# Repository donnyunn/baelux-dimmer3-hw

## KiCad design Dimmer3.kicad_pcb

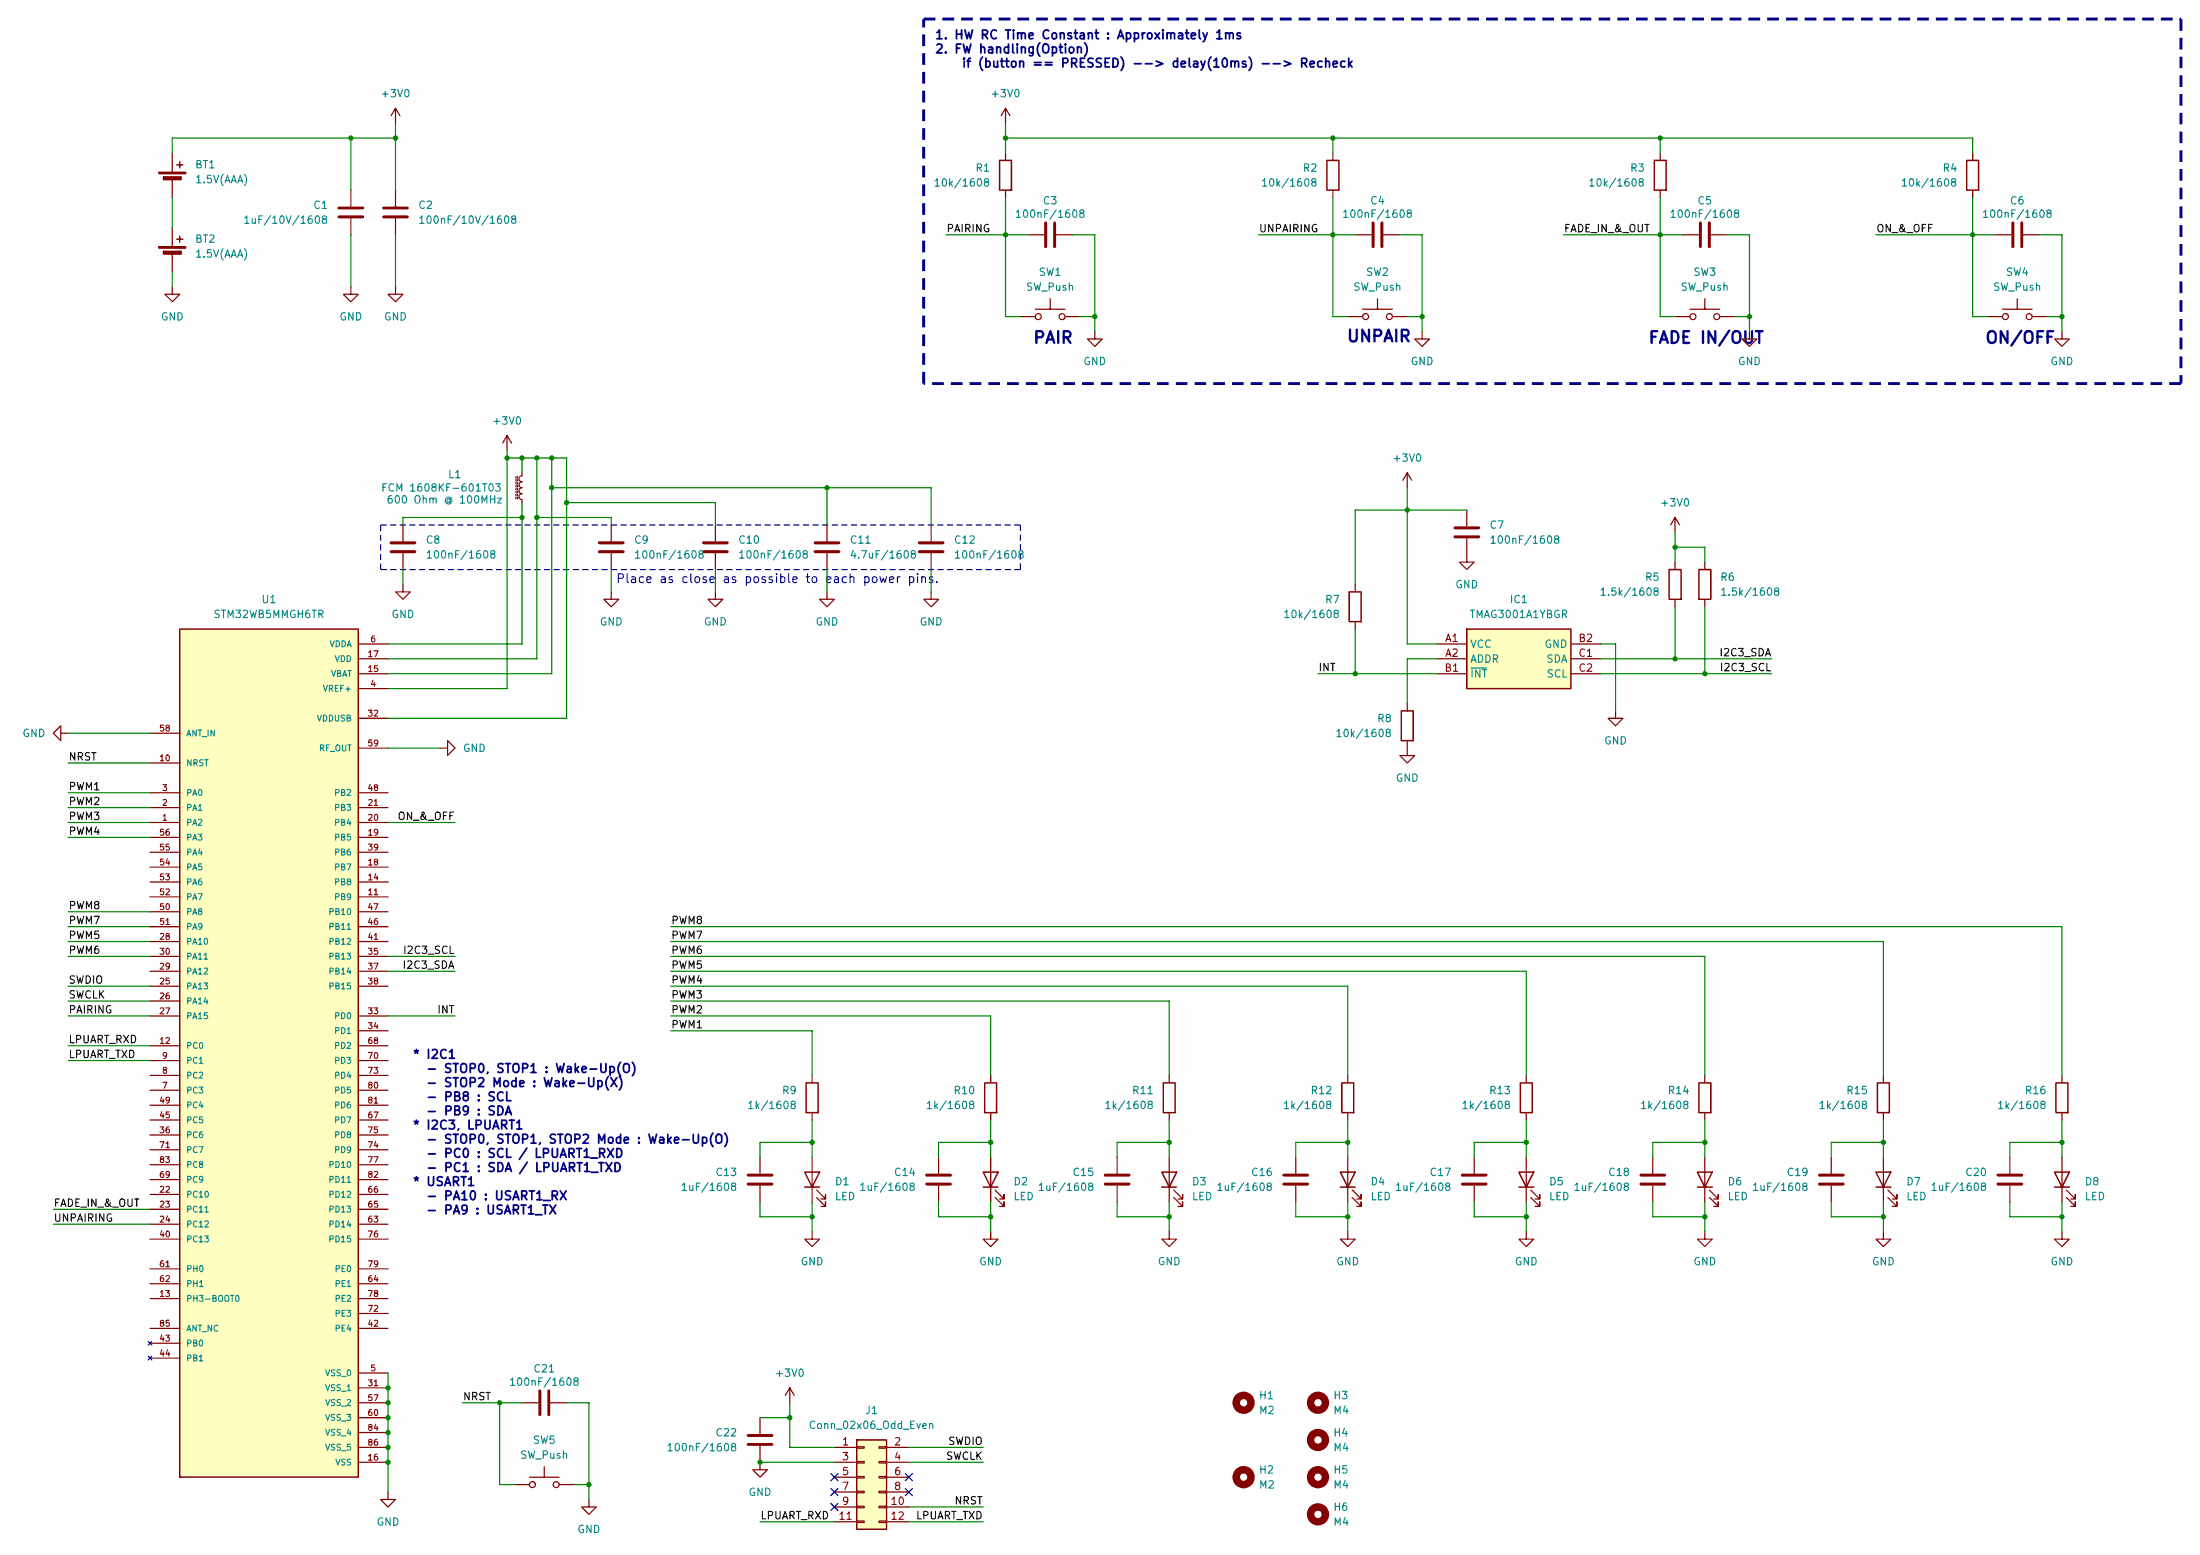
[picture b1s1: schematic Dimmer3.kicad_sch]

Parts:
BT1, BT2: 1.5V(AAA); Battery_spring
C1: 1uF/10V/1608; C_0603_1608Metric; MPN 0603F105Z100CT; LCSC Part# C302042
C2: 100nF/10V/1608; C_0603_1608Metric; MPN CGA0603X7R104K100JT; LCSC Part# C36911391
C3, C4, C5, C6, C7, C8, C9, C10, C12, C21, C22: 100nF/1608; C_0603_1608Metric; MPN CGA0603X7R104K100JT; LCSC Part# C36911391
C11: 4.7uF/1608; C_0603_1608Metric; MPN CL10A475KO8NNNC; LCSC Part# C19666
C13, C14, C15, C16, C17, C18, C19, C20: 1uF/1608; C_0603_1608Metric; MPN 0603F105Z100CT; LCSC Part# C302042
D1, D2, D3, D4, D5, D6, D7, D8: LED; LED_MP-3014-1100-50-80; MPN HL-A-3014S31YC-S1-08HL; LCSC Part# C784732
H1, H2: M2; MountingHole_2.2mm_M2
H3, H4, H5, H6: M4; MountingHole_4.3mm_M4
IC1: TMAG3001A1YBGR; BGA6C40P2X3_79X129X50; Mouser Part Number 595-TMAG3001A1YBGR
J1: Conn_02x06_Odd_Even; PinHeader_2x06_P1.27mm_Vertical
L1: FCM 1608KF-601T03; L_0603_1608Metric_Pad1.05x0.95mm_HandSolder; MPN FCM1608KF-601T03; LCSC Part# C141723
R1, R2, R3, R4, R7, R8: 10k/1608; R_0603_1608Metric; MPN RC0603FR-0710KL; LCSC Part# C98220
R5, R6: 1.5k/1608; R_0603_1608Metric; MPN RC0603FR-071K5L; LCSC Part# C114668
R9, R10, R11, R12, R13, R14, R15, R16: 1k/1608; R_0603_1608Metric; MPN RC0603FR-071KL; LCSC Part# C22548
SW1, SW2, SW3, SW4, SW5: SW_Push; SW_Push_1P1T_XKB_TS-1187A; MPN TS-1087S-01526; LCSC Part# C455262
U1: STM32WB5MMGH6TR; XCVR_STM32WB5MMGH6TR; PARTREV Rev 2; LCSC Part# C5184586

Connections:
+3V0: BT1.1 (+), C1.1, C2.1, C7.1, C9.1, C10.1, C11.1, C12.1, C22.1, IC1.A1 (VCC), J1.1, L1.1, R1.1, R2.1, R3.1, R4.1, R5.1, R6.1, R7.1, U1.4 (VREF+), U1.15 (VBAT), U1.17 (VDD), U1.32 (VDDUSB)
/FADE_IN_&_OUT: C5.1, R3.2, SW3.1, U1.23 (PC11)
/I2C3_SCL: IC1.C2 (SCL), R6.2, U1.35 (PB13)
/I2C3_SDA: IC1.C1 (SDA), R5.2, U1.37 (PB14)
/INT: IC1.B1 (~INT), R7.2, U1.33 (PD0)
/LPUART_RXD: J1.11, U1.12 (PC0)
/LPUART_TXD: J1.12, U1.9 (PC1)
/NRST: C21.1, J1.10, SW5.1, U1.10 (NRST)
/ON_&_OFF: C6.1, R4.2, SW4.1, U1.20 (PB4)
/PAIRING: C3.1, R1.2, SW1.1, U1.27 (PA15)
/PWM1: R9.1, U1.3 (PA0)
/PWM2: R10.1, U1.2 (PA1)
/PWM3: R11.1, U1.1 (PA2)
/PWM4: R12.1, U1.56 (PA3)
/PWM5: R13.1, U1.28 (PA10)
/PWM6: R14.1, U1.30 (PA11)
/PWM7: R15.1, U1.51 (PA9)
/PWM8: R16.1, U1.50 (PA8)
/SWCLK: J1.4, U1.26 (PA14)
/SWDIO: J1.2, U1.25 (PA13)
/UNPAIRING: C4.1, R2.2, SW2.1, U1.24 (PC12)
GND: BT2.2 (-), C1.2, C2.2, C3.2, C4.2, C5.2, C6.2, C7.2, C8.2, C9.2, C10.2, C11.2, C12.2, C13.2, C14.2, C15.2, C16.2, C17.2, C18.2, C19.2, C20.2, C21.2, C22.2, D1.1 (K), D2.1 (K), D3.1 (K), D4.1 (K), D5.1 (K), D6.1 (K), D7.1 (K), D8.1 (K), IC1.B2 (GND), J1.3, R8.2, SW1.2, SW2.2, SW3.2, SW4.2, SW5.2, U1.5 (VSS_0), U1.16 (VSS), U1.31 (VSS_1), U1.57 (VSS_2), U1.58 (ANT_IN), U1.59 (RF_OUT), U1.60 (VSS_3), U1.84 (VSS_4), U1.86 (VSS_5)
unnamed: C13.1, D1.2 (A), R9.2
unnamed: C14.1, D2.2 (A), R10.2
unnamed: C15.1, D3.2 (A), R11.2
unnamed: C16.1, D4.2 (A), R12.2
unnamed: C17.1, D5.2 (A), R13.2
unnamed: C18.1, D6.2 (A), R14.2
unnamed: C19.1, D7.2 (A), R15.2
unnamed: C20.1, D8.2 (A), R16.2
unnamed: IC1.A2 (ADDR), R8.1
unnamed: C8.1, L1.2, U1.6 (VDDA)

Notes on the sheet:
* I2C1 - STOP0, STOP1 : Wake-Up(O) - STOP2 Mode : Wake-Up(X) - PB8 : SCL - PB9 : SDA * I2C3, LPUART1 - STOP0, STOP1, STOP2 Mode : Wake-Up(O) - PC0 : SCL / LPUART1_RXD - PC1 : SDA / LPUART1_TXD * USART1 - PA10 : USART1_RX - PA9 : USART1_TX
FADE IN/OUT
UNPAIR
PAIR
1. HW RC Time Constant : Approximately 1ms 2. FW handling(Option) if (button == PRESSED) --> delay(10ms) --> Recheck
Place as close as possible to each power pins.
ON/OFF

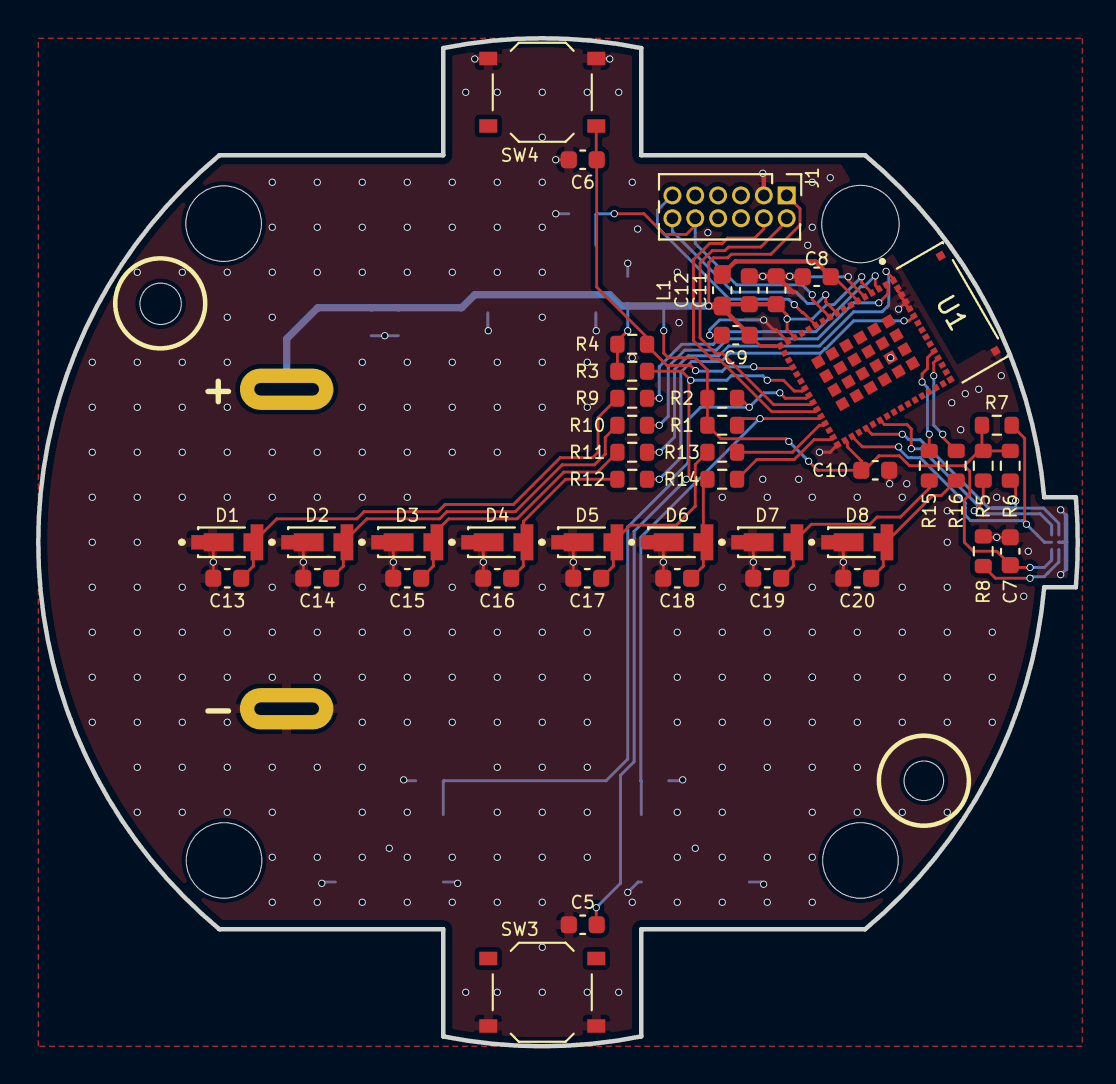
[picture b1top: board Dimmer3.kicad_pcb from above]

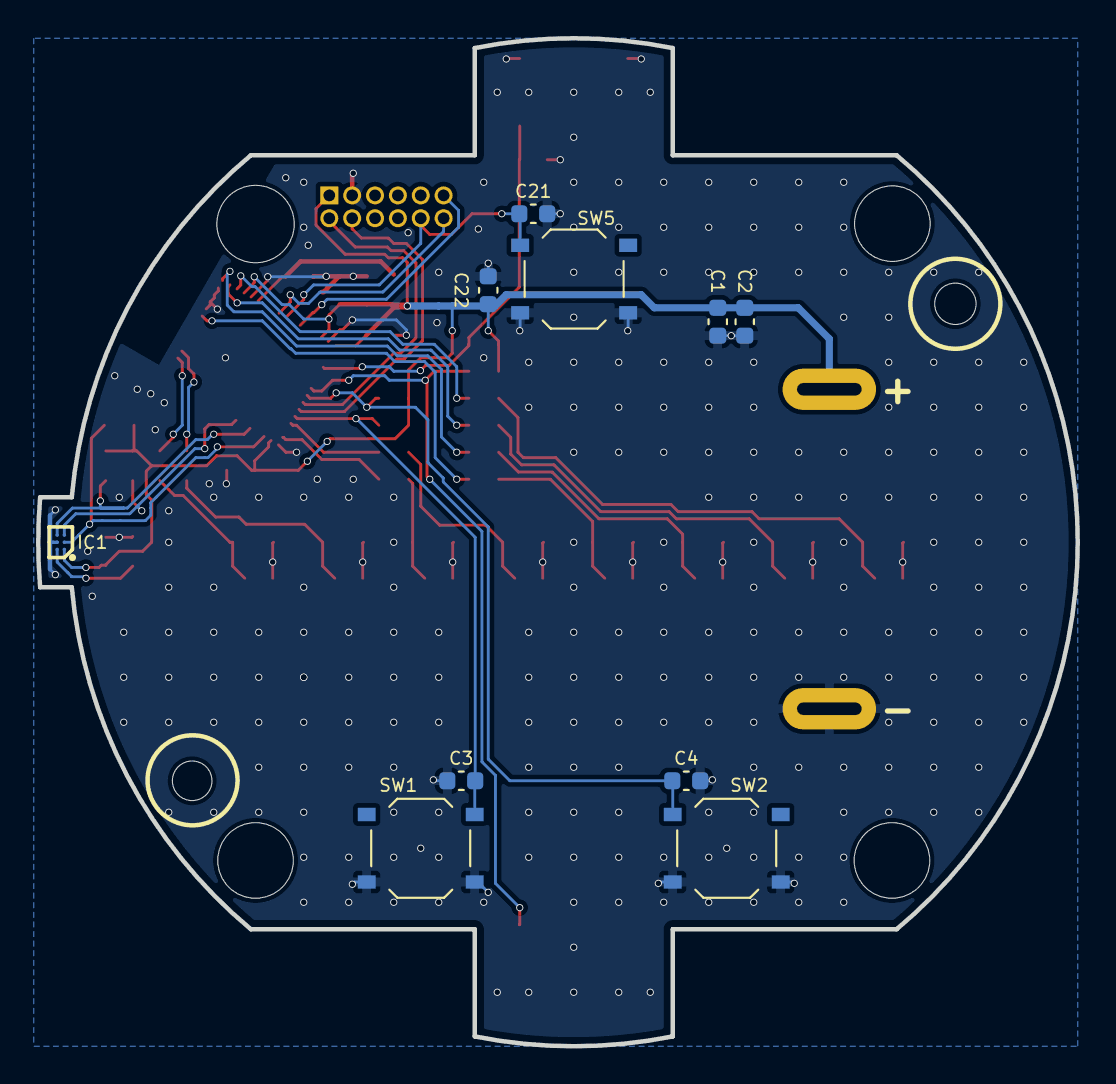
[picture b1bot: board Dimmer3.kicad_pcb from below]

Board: 2 copper layers, 57.7 x 56.0 mm, 63 parts (10 on the bottom side), 32 nets.

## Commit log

2025-10-17 initial work requested on 251016
2025-10-20 modified debug port
